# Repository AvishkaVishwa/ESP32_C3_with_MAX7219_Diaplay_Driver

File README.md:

# ⏰ ESP32‑Powered Smart Clock

> Elegant Wi‑Fi digital clock with MAX7219 4‑digit display, buzzer alarm, and full web control. 

>This project is a Wi-Fi-enabled digital clock built around an ESP32 module that drives a four-digit MAX7219 7-segment display to show real-time hours, minutes, and seconds. A responsive web interface served by the microcontroller lets you set the time, alarms, countdowns, timezone, and home-network credentials, while a buzzer and physical button provide audible alerts and quick dismissal. Running in dual AP/STA mode, the clock creates its own setup hotspot, reconnects to your home Wi-Fi for hourly SNTP synchronization, and stores all settings in NVS for stand-alone, always-accurate operation.
>I did this project to Improve my skills and knowledge in PCB designing and IOT developments.

---

## ✨ Highlights

|                       |                                                                  |
| --------------------- | ---------------------------------------------------------------- |
| **Real‑time display** | Bright 4‑digit 7‑segment driven by MAX7219 (HH\:MM\:SS)          |
| **Responsive web UI** | Set time, alarms, countdown & Wi‑Fi from any browser             |
| **Buzzer & button**   | Loud alarm + physical dismiss (GPIO 0)                           |
| **Dual‑mode Wi‑Fi**   | AP for local control (`Clock` SSID) + STA for internet time sync |
| **SNTP auto‑sync**    | Keeps time accurate to seconds with pool.ntp.org                 |
| **Open hardware**     | KiCad project, 3‑D renders, and BOM included                     |

---

## 🖼️ Gallery

Prototype🙌 
-For the Prototype I used a ESP32 C3 Super Mini Board 

| Web UI                                    | PCB 3‑D                                 | Copper                                  |
| ----------------------------------------- | --------------------------------------- | ------------------------------------------- |
|  |  |  |
                                                                                      
More in [**/assets**](assets) & [**/hardware**](hardware).

<video src ="https://github.com/user-attachments/assets/0d8d9107-081a-4ae7-bd47-be3cfd9f0423"></video>

So when we turned on the clock it takes 10 seconds to connect to the home wifi and connect to the NTP server update the time..

<video src ="https://github.com/user-attachments/assets/e7d40686-c1fc-4405-965b-9b872882c82c"></video>

---

## 🔌 Hardware List

| Qty      | Part                              | Notes                      |
| -------- | --------------------------------- | -------------------------- |
| 1        | **ESP32‑WROOM‑32D** module        | 38‑pin, 4 MB flash         |
| 1        | **MAX7219** 8‑digit driver        | Only digits 0‑3 used       |
| 6        | 1.25" 7‑segment (common cathode) | HHMMSS                     |
| 1        | Piezo buzzer (3 V)                | GPIO 4                     |
| 1        | Tact switch                       | Dismiss, GPIO 0            |
| 2        | LEDs + 1 kΩ                       | Seconds (G2), AM/PM (G19)  |
| 1        | **LM2596S‑5.0** buck              | 12 V → 5 V, feeds 3 V3 LDO |
| assorted | passives, headers                 | See schematic              |

Schematic & PCB files: **`hardware/`** (KiCad 9).

---

## 🗺️ Wiring / Pin Map

```text
ESP32‑WROOM‑32D     MAX7219 / IO       Notes
─────────────────────────────────────────────────
GPIO23  ─────────── DIN      (SPI MOSI)
GPIO18  ─────────── CLK      (SPI SCK)
GPIO5   ─────────── CS       (SPI SS)
GPIO4   ─────────── Buzzer   Active‑high
GPIO0   ─────────── Button   Pulled‑up, boot mode when held
GPIO2   ─────────── Seconds‑LED
GPIO19  ─────────── AM/PM‑LED
3V3/5V  ─────────── VCC      MAX7219 tolerant
GND     ─────────── GND
```

---

## 🚀 Quick Start (Firmware)

```bash
# 1 · Clone and select target
$ git clone https://github.com/AvishkaVishwa/esp32-c3-clock.git
$ cd esp32-c3-clock/firmware
$ idf.py set-target esp32

# 2 · Install submodules & configure
$ git submodule update --init
$ idf.py menuconfig   # Wi‑Fi, timezone, pins, etc.

# 3 · Build, flash & monitor
$ idf.py build flash monitor
```

First boot ➡ creates open AP `Clock` (pwd **clockpass**). Browse to **[http://192.168.4.1](http://192.168.4.1)** to set local time & Wi‑Fi.

> **Tip:** Once connected to your home network the clock pulls NTP every hour.

---

## 🔧 Advanced Options

| Menu                                         | Default              | Description                        |
| -------------------------------------------- | -------------------- | ---------------------------------- |
| `Clock ▸ Timezone`                           | Asia/Colombo (+5:30) | Any UTC offset, 30 min granularity |
| `Clock ▸ Alarms ▸ Alarm 1`                   | 07:00                | Daily repeat                       |
| `Clock ▸ Wi‑Fi ▸ AP SSID`                    | Clock                | Rename if multiple clocks          |
| `Component ▸ HTTP Server ▸ Max URI handlers` | 15                   | Reduce to save RAM                 |

---

## 🎉 Special Thanks to PCBWay

<div align="center">
      
</div>

<p align="center">

</p>

I would like to give a huge shoutout and sincere thanks to **[PCBWay](https://www.pcbway.com/)** for sponsoring the PCB fabrication of this project!

The **build quality, silkscreen clarity, via precision, and copper finish** exceeded expectations. PCBWay’s service was fast, professional, and extremely helpful throughout the production process.

This project wouldn’t have been possible without their generous support. If you’re looking to manufacture professional-grade PCBs at an affordable price, I highly recommend checking them out.

🔗 [Visit PCBWay →](https://www.pcbway.com/)

---

---

> © 2025 Avishka Vishwa   •   Made with ☕ & 🕑

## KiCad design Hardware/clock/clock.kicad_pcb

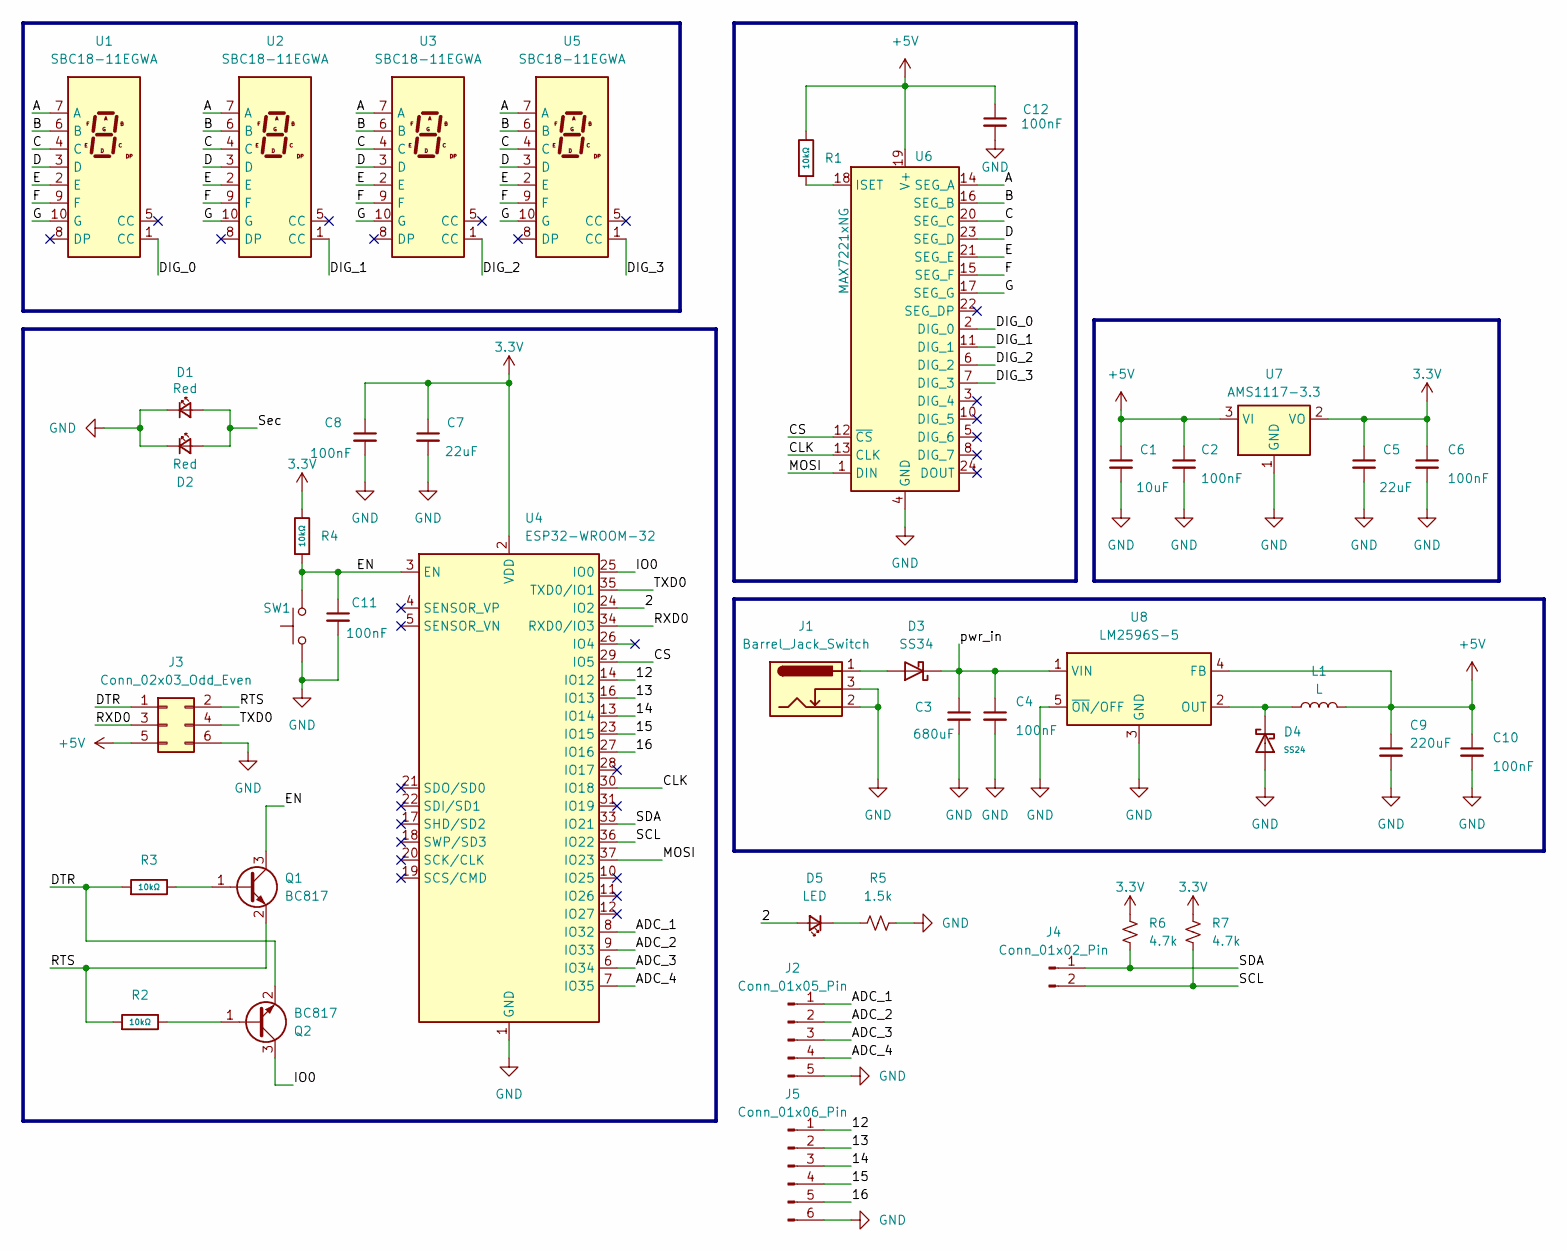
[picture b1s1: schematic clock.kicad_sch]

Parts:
C1: 10uF; CP_Elec_4x5.4; Voltage 1kV; Tolerance 100%
C2, C4, C6, C8, C10, C11, C12: 100nF; C_0805_2012Metric; Voltage 1kV; Tolerance 100%
C3: 680uF; C_Radial_D6.3mm_H7.0mm_P2.50mm; Voltage 1kV; Tolerance 100%
C5: 22uF; 1206; Voltage 1kV; Tolerance 100%
C7: 22uF; C_0805_2012Metric_Pad1.18x1.45mm_HandSolder; Voltage 1kV; Tolerance 100%
C9: 220uF; C_Radial_D6.3mm_H5.0mm_P2.50mm; Voltage 1kV; Tolerance 100%
D1, D2: Red; LED_D3.0mm
D3: SS34; D_SMA
D4: SS24; D_SMA; Forward Voltage (Vf@If) 0.55V@1.0A; Reverse Voltage (Vr) 40V; Part SS24; LCSC C7420362
D5: LED; LED_0603_1608Metric
J1: Barrel_Jack_Switch; BarrelJack_GCT_DCJ200-10-A_Horizontal
J2: Conn_01x05_Pin; PinHeader_1x05_P2.54mm_Vertical
J3: Conn_02x03_Odd_Even; PinHeader_1x06_P2.54mm_Vertical
J4: Conn_01x02_Pin; PinHeader_1x02_P2.00mm_Vertical
J5: Conn_01x06_Pin; PinSocket_1x06_P2.54mm_Vertical
L1: L; L_12x12mm_H8mm
Q1, Q2: BC817; SOT-23
R1, R2, R3, R4: 10kΩ; R_0805; Overload Voltage (Max) 150V; Tolerance ±1%; Part 0805W8F1002T5E; LCSC C17414
R5: 1.5k; R_0603_1608Metric
R6, R7: 4.7k; R_0603_1608Metric
SW1: PTH_RA_h7.5mm; Push_PTH_RA_8-020_h7.5mm; Mfg Part# 8-020 TS H = 7.5mm
U1, U2, U3, U5: SBC18-11EGWA; SBC18-11SURKCGKWA
U4: ESP32-WROOM-32
U6: MAX7221xNG; DIP-24_W7.62mm
U7: AMS1117-3.3; SOT-223-3_TabPin2
U8: LM2596S-5; TO-263-5_TabPin3

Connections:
3.3V: C5.1, C6.1, C7.1, C8.1, R4.2, R6.2, R7.2, U4.2 (VDD), U7.2 (VO)
+5V: C1.1, C2.1, C9.1, C10.1, C12.1, J3.5, L1.2, R1.2, U6.19 (V+), U7.3 (VI), U8.4 (FB)
/2: D5.2 (A), U4.24 (IO2)
/12: J5.1, U4.14 (IO12)
/13: J5.2, U4.16 (IO13)
/14: J5.3, U4.13 (IO14)
/15: J5.4, U4.23 (IO15)
/16: J5.5, U4.27 (IO16)
/A: U1.7 (A), U2.7 (A), U3.7 (A), U5.7 (A), U6.14 (SEG_A)
/ADC_1: J2.1, U4.8 (IO32)
/ADC_2: J2.2, U4.9 (IO33)
/ADC_3: J2.3, U4.6 (IO34)
/ADC_4: J2.4, U4.7 (IO35)
/B: U1.6 (B), U2.6 (B), U3.6 (B), U5.6 (B), U6.16 (SEG_B)
/C: U1.4 (C), U2.4 (C), U3.4 (C), U5.4 (C), U6.20 (SEG_C)
/CLK: U4.30 (IO18), U6.13 (CLK)
/CS: U4.29 (IO5), U6.12 (~CS)
/D: U1.3 (D), U2.3 (D), U3.3 (D), U5.3 (D), U6.23 (SEG_D)
/DIG_0: U1.1 (CC), U6.2 (DIG_0)
/DIG_1: U2.1 (CC), U6.11 (DIG_1)
/DIG_2: U3.1 (CC), U6.6 (DIG_2)
/DIG_3: U5.1 (CC), U6.7 (DIG_3)
/DTR: J3.1, Q2.2 (E), R3.1
/E: U1.2 (E), U2.2 (E), U3.2 (E), U5.2 (E), U6.21 (SEG_E)
/EN: C11.1, Q1.3 (C), R4.1, SW1.2, U4.3 (EN)
/F: U1.9 (F), U2.9 (F), U3.9 (F), U5.9 (F), U6.15 (SEG_F)
/G: U1.10 (G), U2.10 (G), U3.10 (G), U5.10 (G), U6.17 (SEG_G)
/IO0: Q2.3 (C), U4.25 (IO0)
/MOSI: U4.37 (IO23), U6.1 (DIN)
/RTS: J3.2, Q1.2 (E), R2.1
/RXD0: J3.3, U4.34 (RXD0/IO3)
/SCL: J4.2, R7.1, U4.36 (IO22)
/SDA: J4.1, R6.1, U4.33 (IO21)
/Sec: D1.2 (A), D2.2 (A)
/TXD0: J3.4, U4.35 (TXD0/IO1)
/pwr_in: C3.1, C4.1, D3.1 (K), U8.1 (VIN)
GND: C1.2, C2.2, C3.2, C4.2, C5.2, C6.2, C7.2, C8.2, C9.2, C10.2, C11.2, C12.2, D1.1 (K), D2.1 (K), D4.2, J1.2, J1.3, J2.5, J3.6, J5.6, R5.2, SW1.1, U4.1 (GND), U4.15 (GND), U4.38 (GND), U4.39 (GND), U6.4 (GND), U6.9 (GND), U7.1 (GND), U8.3 (GND), U8.5 (~ON/OFF)
unnamed: D3.2 (A), J1.1
unnamed: D5.1 (K), R5.1
unnamed: Q1.1 (B), R3.2
unnamed: Q2.1 (B), R2.2
unnamed: R1.1, U6.18 (ISET)
unnamed: D4.1, L1.1, U8.2 (OUT)

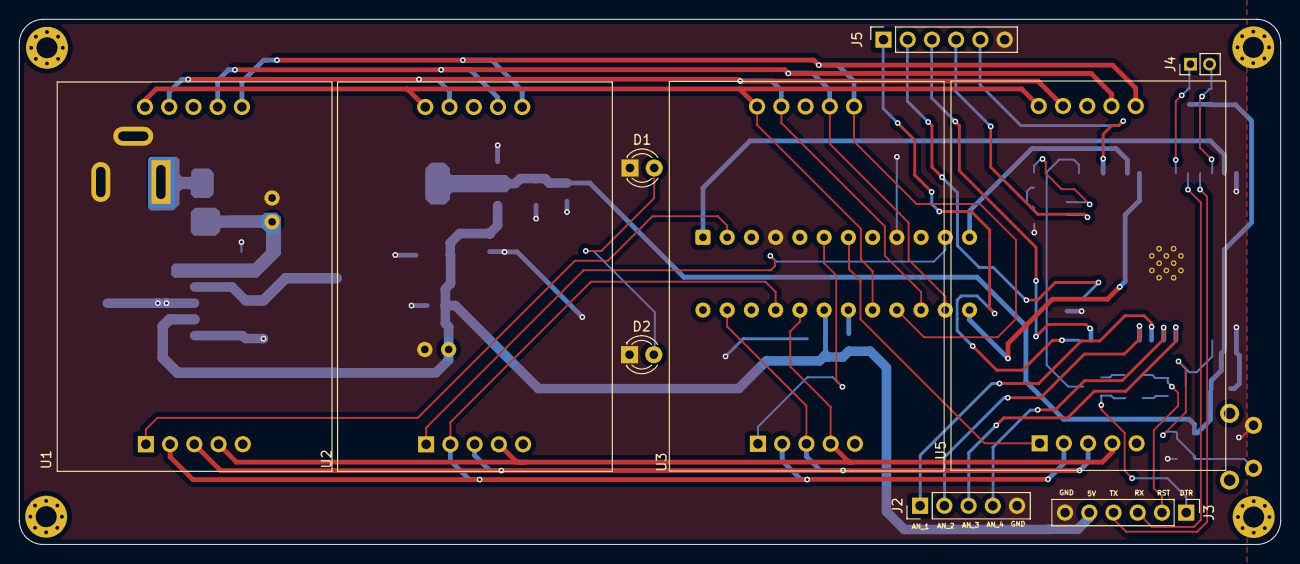
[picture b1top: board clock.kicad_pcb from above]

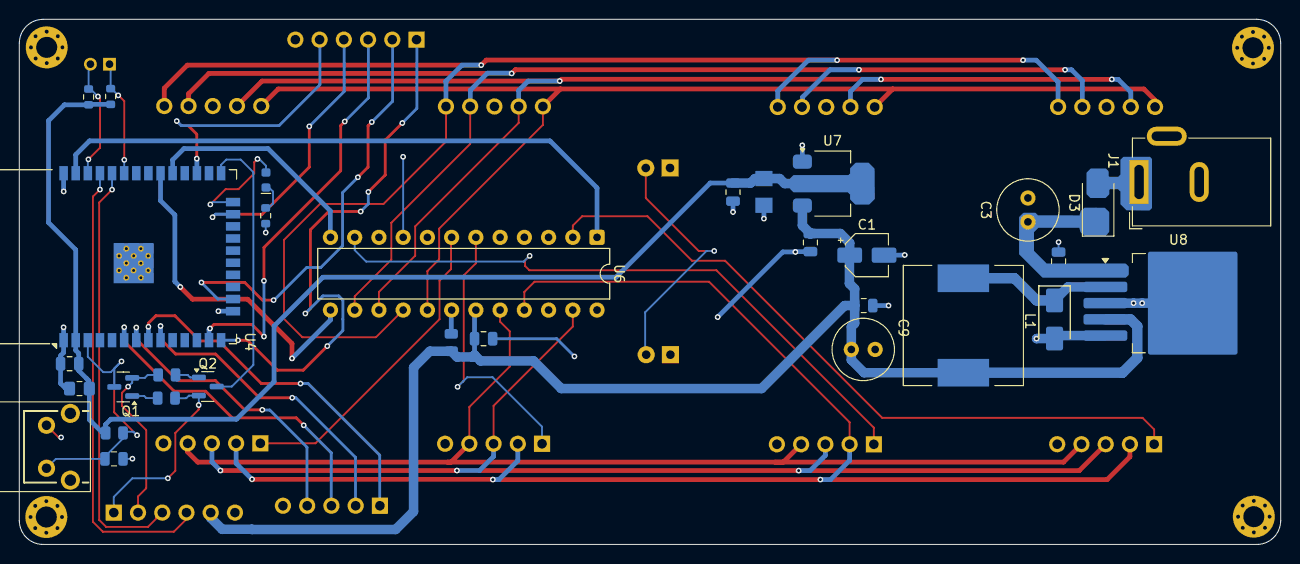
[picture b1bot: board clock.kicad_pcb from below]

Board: 2 copper layers, 132.2 x 55.0 mm, 41 parts (31 on the bottom side), 43 nets.

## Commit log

2025-06-06 Initial project setup for ESP-IDF clock application with Docker support, web server functionality, and alarm features.
2025-06-06 Update README.md to provide detailed project documentation for ESP32-C3 digital clock with web interface
2025-06-06 Refactor code structure for improved readability and maintainability
2025-06-06 Remove license and contributing sections from README.md
2025-06-06 Remove introductory line from README.md
2025-06-06 Update project title in README.md to include MAX7219 Display Driver
2025-06-13 - Updated component metadata with versioning and licensing information.
2025-06-16 Add lock file for clock schematic with hostname and username information
2025-06-19 Update README.md to correct image paths and enhance PCB design section
2025-06-19 Remove roadmap section from README.md
2025-06-19 Fix PCB render image path in README.md
2025-06-19 Add missing PCB render images to README.md
2025-06-26 Add initial PCB lock file and component list for clock project
    - Created a lock file for the PCB design with hostname and username.
    - Added a comprehensive CSV file listing components for the clock project, including values, footprints, and datasheets for each component.
2025-06-26 Update ESP-IDF configurations to target esp32 and correct compiler path
2025-06-27 Add CHECKSUMS.json for zorxx__rtci2c component with file hashes and metadata
2025-06-29 Update README.md to enhance gallery section and add special thanks to PCBWay for project sponsorship
2025-06-29 Implement code changes to enhance functionality and improve performance
2025-06-29 Update README.md to enhance the special thanks section with additional images
2025-06-29 Update README.md to center-align images in the special thanks section
2025-06-29 Fix layout in special thanks section by removing separator between images
2025-06-29 Update special thanks section layout for improved image alignment
2025-06-29 Remove badge section from README.md for a cleaner layout
2025-06-29 Add missing image in the gallery section of README.md
2025-06-29 Fix layout in gallery section by consolidating image tags for better alignment
2025-06-29 Fix image source in gallery section for correct display
2025-06-29 Add video demonstration to the gallery section in README.md
2025-06-29 Add explanation of clock's Wi-Fi connection time to README.md
2025-06-29 Remove contributing section from README.md
2025-06-29 Refine project description and remove license section from README.md
2025-06-29 Add acknowledgment for PCBWay sponsorship in README.md
2025-06-29 Add initial clock component definitions to clock.csv
2025-06-29 Remove NPTH and PTH drill files along with the associated job file for the clock project to streamline the design and eliminate unnecessary components.
2025-06-29 Update README.md to include additional prototype images for better visualization
2025-06-29 Fix display description in README.md to reflect 4-digit MAX7219 configuration
2025-06-29 Update README.md to correct 7-segment display size from 0.56" to 1.25"
2025-06-29 Update README.md to correct MAX7219 driver digit usage from 0-5 to 0-3
2025-06-29 Remove factory test routine section from README.md
2025-06-29 Fix formatting in README.md by removing unnecessary pipe in image alignment
2025-07-14 feat: Initial implementation of ESP32 Clock application
    - Added app_config.h for configuration constants and global variables.
    - Implemented display_manager for controlling MAX7219 display.
    - Created max7219 driver for handling display commands.
    - Developed time_utils for managing time synchronization and settings.
    - Established web_server for handling HTTP requests for clock settings.
    - Implemented wifi_manager for managing WiFi connections and configurations.
